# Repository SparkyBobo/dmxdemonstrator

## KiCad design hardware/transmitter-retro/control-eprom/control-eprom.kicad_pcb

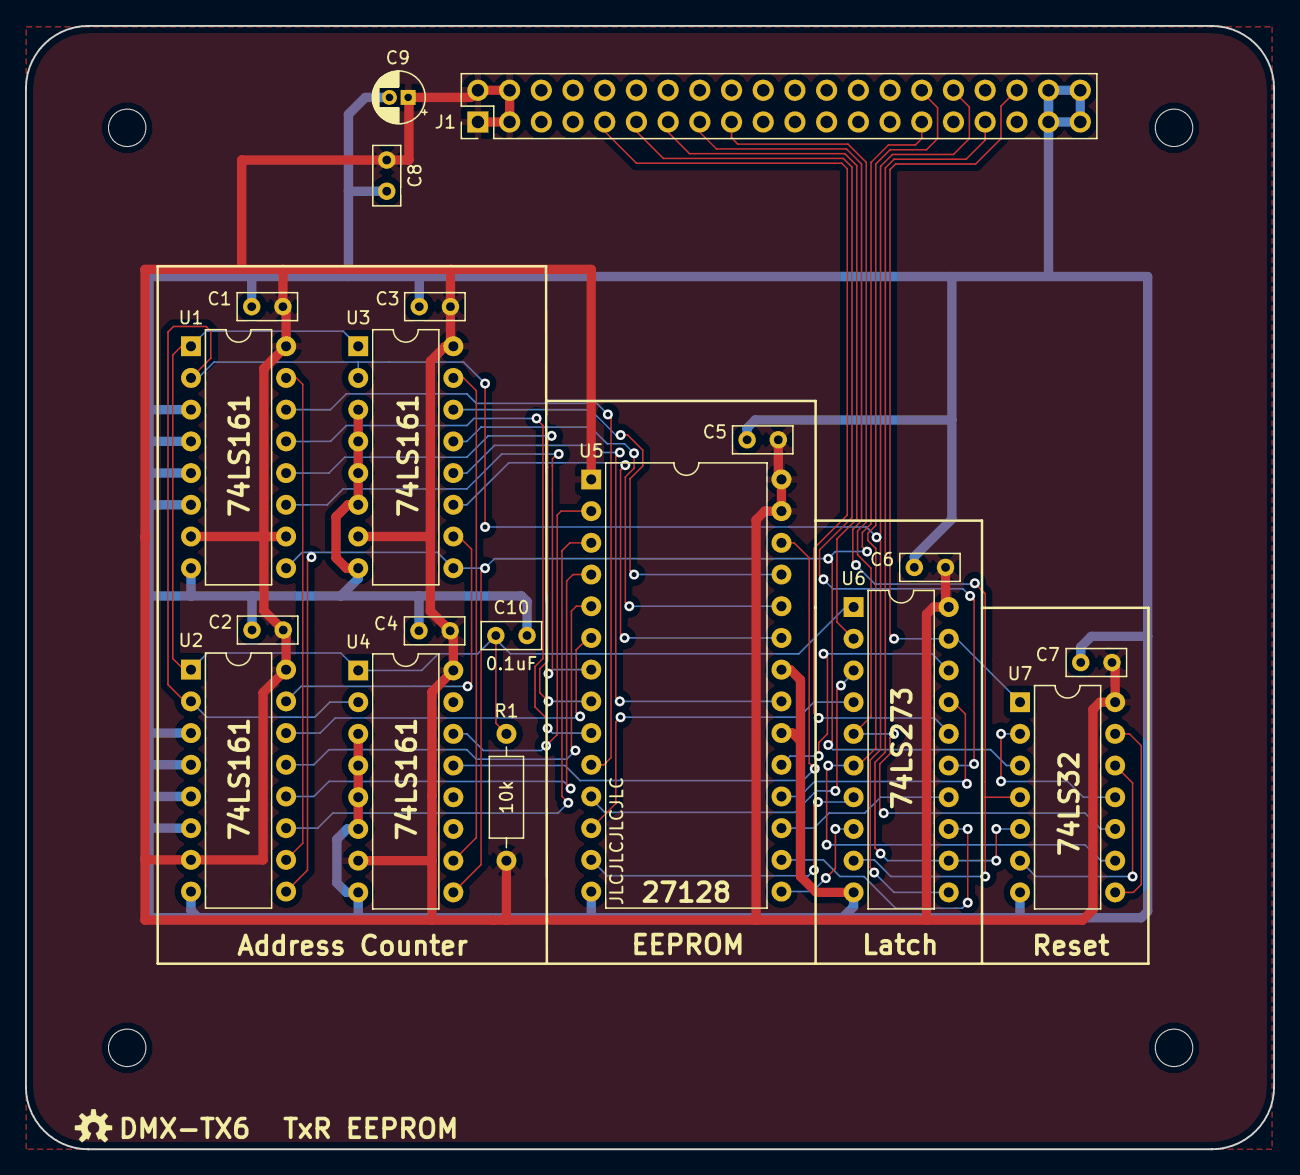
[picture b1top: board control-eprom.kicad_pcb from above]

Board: 2 copper layers, 100.0 x 90.0 mm, 23 parts (0 on the bottom side), 41 nets.

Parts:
C1, C2, C3, C4, C5, C6, C7, C8, C10: 0.1uF; C_Rect_L4.6mm_W2.0mm_P2.50mm_MKS02_FKP02
C9: 10uF; CP_Radial_D4.0mm_P1.50mm
J1: Expansion; PinHeader_2x20_P2.54mm_Vertical
MH1, MH2, MH3, MH4: MountingHole; MountingHole_3mm
R1: 10k; R_Axial_DIN0207_L6.3mm_D2.5mm_P10.16mm_Horizontal
U1, U2, U3, U4: 74LS161; DIP-16_W7.62mm
U5: 27128; DIP-28_W15.24mm
U6: 74LS273; DIP-20_W7.62mm
U7: 74LS32; DIP-14_W7.62mm

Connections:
+5V: C1.1, C2.1, C3.1, C4.1, C5.1, C6.1, C7.1, C8.1, C9.1, J1.1, J1.2, J1.3, J1.4, R1.1, U1.7, U1.10, U1.16, U2.7, U2.16, U3.7, U3.16, U4.7, U4.16, U5.1, U5.27, U5.28, U6.20, U7.14
/CARRY_0: U1.15, U2.10
/CARRY_1: U2.15, U3.10
/CARRY_2: U3.15, U4.10
/CLK_TX: J1.32, U1.2, U2.2, U3.2, U4.2, U6.11
/DATA_FIXED: J1.13, U6.2
/IA0: U1.14, U5.10
/IA1: U1.13, U5.9
/IA2: U1.12, U5.8
/IA3: U1.11, U5.7
/IA4: U2.14, U5.6
/IA5: U2.13, U5.5
/IA6: U2.12, U5.4
/IA7: U2.11, U5.3
/IA8: U3.14, U5.25
/IA9: U3.13, U5.24
/IA10: U3.12, U5.21
/IA11: U3.11, U5.23
/IA12: U4.14, U5.2
/IA13: U4.13, U5.26
/SAMPLE_LATCH: J1.36, U6.19, U7.1
/SAMPLE_SEL0: J1.11, U6.15
/SAMPLE_SEL1: J1.9, U6.16
/SHIFT_TRANSMIT: J1.17, U6.5, U7.10
/~FRAME_RESET: J1.29, U1.9, U2.9, U3.9, U4.9, U7.3
/~SAMPLE_RESET: J1.33, U6.12, U7.5
/~SHIFT_ENABLE: J1.30, U6.6, U7.9
/~SHIFT_LOAD: J1.15, U6.9, U7.4
GND: C1.2, C2.2, C3.2, C4.2, C5.2, C6.2, C7.2, C8.2, C9.2, C10.2, J1.37, J1.38, J1.39, J1.40, U1.3, U1.4, U1.5, U1.6, U1.8, U2.3, U2.4, U2.5, U2.6, U2.8, U3.3, U3.4, U3.5, U3.6, U3.8, U4.3, U4.4, U4.5, U4.6, U4.8, U5.14, U5.20, U5.22, U6.10, U7.7
unnamed: C10.1, R1.2, U1.1, U2.1, U3.1, U4.1, U6.1
unnamed: U5.11, U6.3
unnamed: U5.12, U6.4
unnamed: U5.13, U6.7
unnamed: U5.15, U6.8
unnamed: U5.16, U6.13
unnamed: U5.17, U6.14
unnamed: U5.18, U6.17
unnamed: U5.19, U6.18
unnamed: U7.2, U7.11
unnamed: U7.6, U7.12
unnamed: U7.8, U7.13

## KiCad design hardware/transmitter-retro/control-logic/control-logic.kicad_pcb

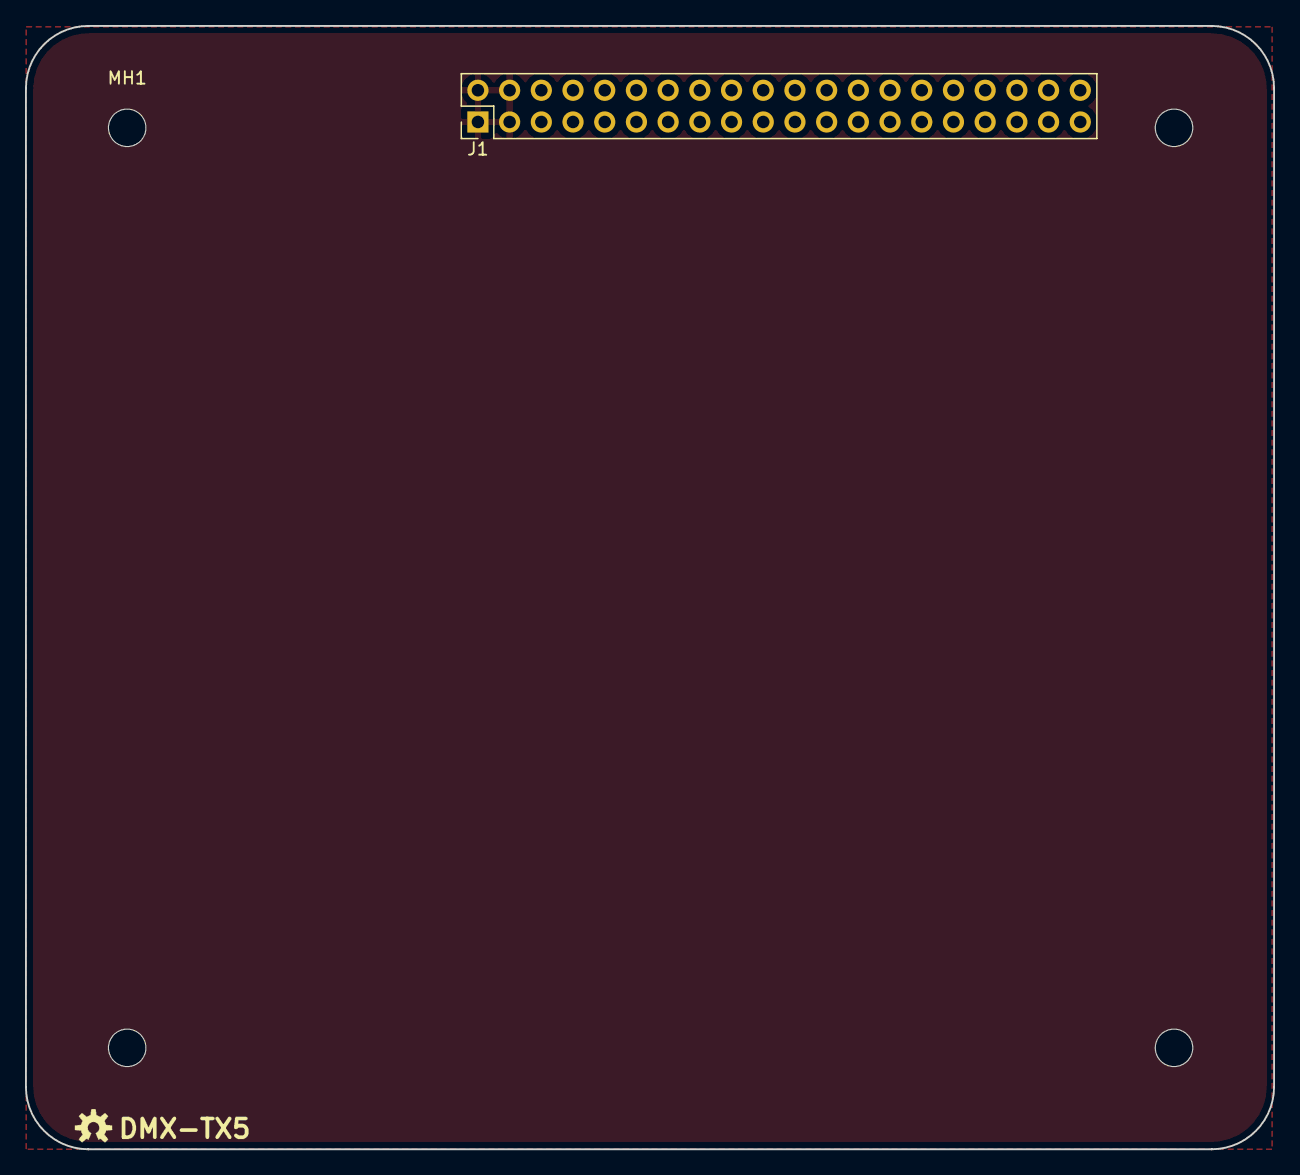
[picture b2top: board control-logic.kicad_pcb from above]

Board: 2 copper layers, 100.0 x 90.0 mm, 5 parts (0 on the bottom side), 2 nets, no tracks yet.

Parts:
J1: Expansion; PinHeader_2x20_P2.54mm_Vertical
MH1, MH2, MH3, MH4: MountingHole; MountingHole_3mm

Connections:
+5V: J1.1, J1.2, J1.3, J1.4
GND: J1.37, J1.38, J1.39, J1.40

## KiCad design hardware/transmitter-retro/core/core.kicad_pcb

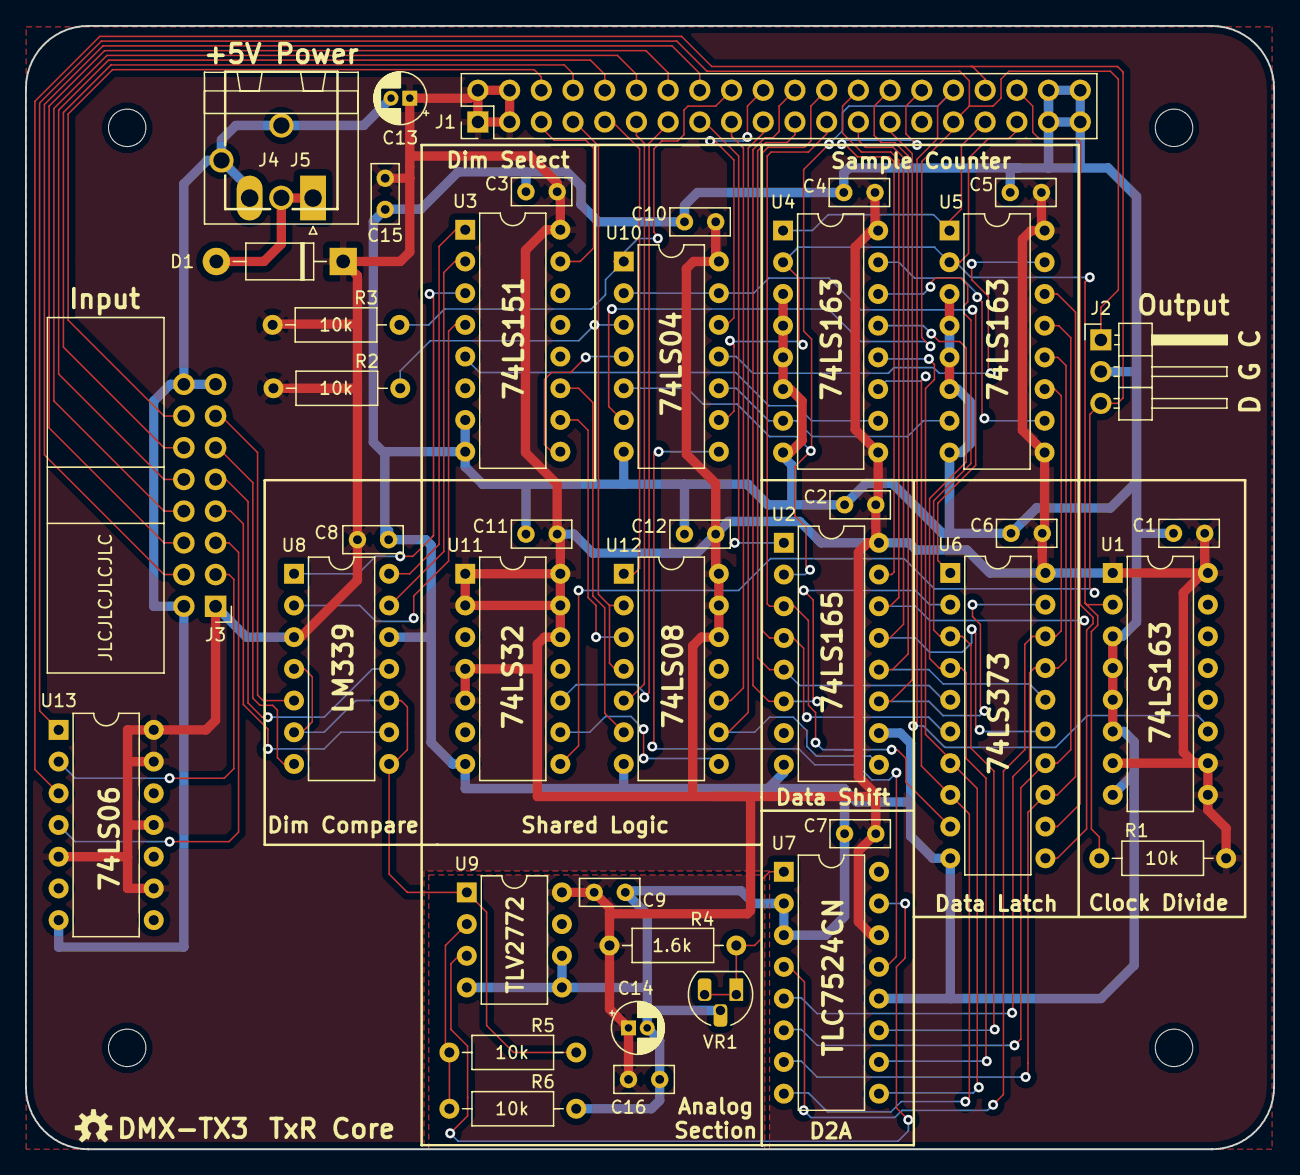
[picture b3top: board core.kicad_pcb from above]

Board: 2 copper layers, 100.0 x 90.0 mm, 46 parts (0 on the bottom side), 66 nets.

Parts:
C1, C2, C3, C4, C5, C6, C7, C8, C9, C10, C11, C12, C15, C16: 0.1uF; C_Rect_L4.6mm_W2.0mm_P2.50mm_MKS02_FKP02
C13, C14: 10uF; CP_Radial_D4.0mm_P1.50mm
D1: 1N5822; D_DO-41_SOD81_P10.16mm_Horizontal
J1: Expansion; PinHeader_2x20_P2.54mm_Vertical
J2: Output; PinHeader_1x03_P2.54mm_Horizontal
J3: Input; IDC-Header_2x08_P2.54mm_Horizontal
J4: Power; PhoenixContact_MSTBA_2,5_2-G-5,08_1x02_P5.08mm_Horizontal
J5: Power; POWER_JACK_PTH_BREAD
MH1, MH2, MH3, MH4: MountingHole; MountingHole_3mm
R1, R2, R3, R5, R6: 10k; R_Axial_DIN0207_L6.3mm_D2.5mm_P10.16mm_Horizontal
R4: 1.6k; R_Axial_DIN0207_L6.3mm_D2.5mm_P10.16mm_Horizontal
U1, U4, U5: 74LS163; DIP-16_W7.62mm
U2: 74LS165; DIP-16_W7.62mm
U3: 74LS151; DIP-16_W7.62mm
U6: 74LS373; DIP-20_W7.62mm
U7: TLC7524CN; DIP-16_W7.62mm
U8: LM339; DIP-14_W7.62mm
U9: TLV2772CP; DIP-8_W7.62mm
U10: 74LS04; DIP-14_W7.62mm
U11: 74LS32; DIP-14_W7.62mm
U12: 74LS08; DIP-14_W7.62mm
U13: 74LS06; DIP-14_W7.62mm
VR1: TL1431; TO-92L_HandSolder

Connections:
+5V: C1.1, C2.1, C3.1, C4.1, C5.1, C6.1, C7.1, C8.1, C9.1, C10.1, C11.1, C12.1, C13.1, C14.1, C15.1, C16.1, D1.1, J1.1, J1.2, J1.3, J1.4, J3.1, R1.2, R2.1, R3.1, R4.2, U1.1, U1.7, U1.9, U1.10, U1.16, U2.16, U3.16, U4.9, U4.16, U5.9, U5.16, U6.20, U7.14, U8.3, U9.8, U10.14, U11.1, U11.2, U11.4, U11.5, U11.12, U11.13, U11.14, U12.12, U12.13, U12.14, U13.5, U13.9, U13.11, U13.13, U13.14
/CLK_RX: J1.31, J2.1, U10.6, U13.1
/CLK_SAMPLE: J1.35, R1.1, U1.2, U4.2, U5.2, U10.9
/CLK_TX: J1.32, U1.11, U2.2, U10.5
/D0: J1.22, U2.6, U6.2
/D1: J1.21, U2.5, U6.5
/D2: J1.24, U2.4, U6.6
/D3: J1.23, U2.3, U6.9
/D4: J1.26, U2.14, U6.12
/D5: J1.25, U2.13, U6.15
/D6: J1.28, U2.12, U6.16
/D7: J1.27, U2.11, U6.19
/DATA_FIXED: J1.13, U11.10
/DATA_RX: J1.34, J2.3, U11.8, U13.3
/DATA_SHIFT: J1.19, U2.9, U12.9
/DIM1: J3.7, U8.9
/DIM2: J3.9, U8.11
/DIM3: J3.11, U8.7
/DIM4: J3.13, U8.5
/SAMPLE_COUNT: J1.5, U3.15
/SAMPLE_LATCH: J1.36, U6.11
/SAMPLE_SEL0: J1.11, U12.5
/SAMPLE_SEL1: J1.9, U12.1
/SHIFT_TRANSMIT: J1.17, U12.10
/SPD_HI: J1.16, J3.4
/SPD_LO: J1.12, J3.8
/SPD_MID: J1.14, J3.6
/sample/DO0: U4.14, U6.3, U7.11
/sample/DO1: U4.13, U6.4, U7.10
/sample/DO2: U4.12, U6.7, U7.9
/sample/DO3: U4.11, U6.8, U7.8
/sample/DO4: U5.14, U6.13, U7.7
/sample/DO5: U5.13, U6.14, U7.6
/sample/DO6: U5.12, U6.17, U7.5
/sample/DO7: U5.11, U6.18, U7.4
/~BUS_ACK: J1.20, U10.12
/~BUS_REQ: J1.18, R3.2, U10.1
/~CLK_FST: J1.6, J3.14
/~CLK_SLO: J1.8, J3.12
/~CLK_STEP: J1.10, J3.10
/~CLOCK: J3.3, U13.2
/~DATA: J3.5, U13.4
/~SAMPLE_OVERRIDE: J1.7, R2.2, U10.3, U12.2, U12.4
/~SAMPLE_RESET: J1.33, U4.1, U5.1
/~SHIFT_ENABLE: J1.30, U2.15
/~SHIFT_LOAD: J1.15, U2.1
GND: C1.2, C2.2, C3.2, C4.2, C5.2, C6.2, C7.2, C8.2, C9.2, C10.2, C11.2, C12.2, C13.2, C14.2, C15.2, C16.2, J1.37, J1.38, J1.39, J1.40, J2.2, J3.2, J3.15, J3.16, J4.2, J5.GND, J5.GNDB, R6.1, U1.3, U1.4, U1.5, U1.6, U1.8, U2.8, U2.10, U3.7, U3.8, U4.3, U4.4, U4.5, U4.6, U4.8, U5.3, U5.4, U5.5, U5.6, U5.8, U6.10, U7.2, U7.3, U7.12, U8.12, U9.4, U9.5, U9.6, U10.7, U11.7, U12.7, U13.7, VR1.2
unnamed: D1.2, J4.1, J5.PWR
unnamed: R4.1, U7.1, VR1.1, VR1.3
unnamed: R5.1, R6.2, U9.2
unnamed: R5.2, U8.4, U8.6, U8.8, U8.10, U9.1
unnamed: U3.1, U8.14
unnamed: U3.2, U8.13
unnamed: U3.3, U8.1
unnamed: U3.4, U8.2
unnamed: U3.5, U4.10
unnamed: U4.15, U5.10
unnamed: U7.15, U9.3
unnamed: U3.9, U10.4
unnamed: U7.13, U10.8
unnamed: U4.7, U5.7, U10.10
unnamed: U5.15, U10.11
unnamed: U6.1, U10.2, U10.13
unnamed: U11.9, U12.8
unnamed: U3.10, U12.3
unnamed: U3.11, U12.6

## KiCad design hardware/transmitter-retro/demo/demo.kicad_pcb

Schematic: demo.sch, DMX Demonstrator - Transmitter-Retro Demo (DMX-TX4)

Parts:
A1: Monitor; Arduino_Nano
J1: Expansion; PinHeader_2x20_P2.54mm_Vertical
NT1: Tie; NetTie-2_THT_Pad0.3mm

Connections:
+5V: A1.3 (RESET), A1.28 (RESET), J1.1, J1.2, J1.3, J1.4, NT1.2; also elsewhere on the board
/CLK_RX: A1.16 (D13), J1.31; also elsewhere on the board
/CLK_SAMPLE: J1.35; also elsewhere on the board
/D0: A1.26 (A7), J1.22
/D1: A1.25 (A6), J1.21
/D2: A1.24 (A5), J1.24
/D3: A1.23 (A4), J1.23
/D4: A1.22 (A3), J1.26
/D5: A1.21 (A2), J1.25
/D6: A1.20 (A1), J1.28
/D7: A1.19 (A0), J1.27
/DATA_RX: A1.15 (D12), J1.34
/SAMPLE_LATCH: A1.12 (D9), J1.36
/SAMPLE_SEL0: A1.6 (D3), J1.11
/SAMPLE_SEL1: A1.5 (D2), J1.9
/SHIFT_TRANSMIT: A1.9 (D6), J1.17
/SPD_LO: J1.12; also elsewhere on the board
/SPD_MID: J1.14; also elsewhere on the board
/step/~CLK_S0_IN: A1.13 (D10); also elsewhere on the board
/step/~CLK_S1_IN: A1.14 (D11); also elsewhere on the board
/step/~CLK_STEPB_IN: A1.1 (D1/TX); also elsewhere on the board
/~CLK_FST: J1.6; also elsewhere on the board
/~CLK_SLO: J1.8; also elsewhere on the board
/~CLK_STEP: J1.10; also elsewhere on the board
/~FRAME_RESET: A1.7 (D4), J1.29
/~SAMPLE_RESET: A1.11 (D8), J1.33
/~SHIFT_ENABLE: A1.10 (D7), J1.30
/~SHIFT_LOAD: A1.8 (D5), J1.15
GND: A1.4 (GND), A1.29 (GND), J1.37, J1.38, J1.39, J1.40; also elsewhere on the board
unnamed: A1.27 (+5V), NT1.1

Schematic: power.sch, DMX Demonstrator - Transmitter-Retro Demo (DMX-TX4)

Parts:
C1, C2, C3, C4, C5, C6, C7, C11, C12: 0.1uF; C_Rect_L4.6mm_W2.0mm_P2.50mm_MKS02_FKP02
C9, C10: 10uF; CP_Radial_D4.0mm_P1.50mm
MH1, MH2, MH3, MH4: MountingHole; MountingHole_3mm
U3, U4, U5: 74LS74; DIP-14_W7.62mm
U6: 74LS08; DIP-14_W7.62mm
U7: 74LS32; DIP-14_W7.62mm

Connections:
+5V: C1.1, C2.1, C3.1, C4.1, C5.1, C6.1, C7.1, C9.1, C10.1, C11.1, C12.1, U3.4, U3.10, U3.14, U4.4, U4.10, U4.14, U5.4, U5.14, U6.12, U6.13, U6.14, U7.1, U7.2, U7.4, U7.5, U7.12, U7.13, U7.14; also elsewhere on the board
/CLK_RX: U5.11; also elsewhere on the board
/step/CLK_FAST_IN: U3.3, U3.11, U4.3, U4.11, U5.3; also elsewhere on the board
/step/CLK_SEND_ENABLE: U5.1, U5.8
/step/CLK_STEP_MODE: U6.3, U6.9
/step/CLK_STEP_OUT: U5.5; also elsewhere on the board
/step/~CLK_S0_IN: U3.5, U6.1; also elsewhere on the board
/step/~CLK_S1_IN: U3.9, U6.2; also elsewhere on the board
/step/~CLK_STEPB_IN: U6.4; also elsewhere on the board
/step/~CLK_STEPIN: U4.5, U4.12, U7.9
/step/~CLK_STEP_PULSE: U5.13, U6.8
/~CLK_FST: U3.12; also elsewhere on the board
/~CLK_SLO: U3.2; also elsewhere on the board
/~CLK_STEP: U6.5; also elsewhere on the board
GND: C1.2, C2.2, C3.2, C4.2, C5.2, C6.2, C7.2, C9.2, C10.2, C11.2, C12.2, U3.7, U4.7, U5.7, U6.7, U7.7; also elsewhere on the board
unnamed 44: U3.1, U3.13; also elsewhere on the board
unnamed 45: U4.1, U4.13, U5.10, U5.12; also elsewhere on the board
unnamed: U4.2, U6.6
unnamed: U4.8, U7.10
unnamed: U5.2, U5.6
unnamed: U6.10, U7.8

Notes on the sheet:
Logic IC Power
Decoupling Capacitors
Unused Gates

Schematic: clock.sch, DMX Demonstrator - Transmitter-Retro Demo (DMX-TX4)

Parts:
C13: 0.47uF; C_Rect_L4.6mm_W2.0mm_P2.50mm_MKS02_FKP02
C14, C15, C17: 0.1uF; C_Rect_L4.6mm_W2.0mm_P2.50mm_MKS02_FKP02
C16: .001uF; C_Rect_L4.6mm_W2.0mm_P2.50mm_MKS02_FKP02
R2: 100; R_Axial_DIN0207_L6.3mm_D2.5mm_P10.16mm_Horizontal
R3: 330; R_Axial_DIN0207_L6.3mm_D2.5mm_P10.16mm_Horizontal
R4, R5, R6, R7, R8: 10k; R_Axial_DIN0207_L6.3mm_D2.5mm_P10.16mm_Horizontal
U1: 556; DIP14
U2: 74LS151; DIP-16_W7.62mm
U3: 74LS74; DIP-14_W7.62mm

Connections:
+5V: R3.1, R4.1, R6.1, R7.1, R8.1, U1.4, U1.10, U1.14, U2.4, U2.12, U2.13, U2.14, U2.15, U2.16, U3.4, U3.10, U3.14; also elsewhere on the board
/CLK_SAMPLE: U2.5; also elsewhere on the board
/SPD_LO: C13.1, U1.2, U1.6; also elsewhere on the board
/SPD_MID: R2.2; also elsewhere on the board
/clock/CLK_SLOW: U1.5, U2.2
/step/CLK_FAST_IN: U1.9, U2.3, U3.3, U3.11; also elsewhere on the board
/step/CLK_STEP_OUT: U2.1; also elsewhere on the board
/step/~CLK_S0_IN: U2.11, U3.5; also elsewhere on the board
/step/~CLK_S1_IN: U2.10, U3.9; also elsewhere on the board
/~CLK_FST: R7.2, U3.12; also elsewhere on the board
/~CLK_SLO: R6.2, U3.2; also elsewhere on the board
GND: C13.2, C14.2, C15.2, C16.2, C17.2, U1.7, U2.7, U2.8, U2.9, U3.7; also elsewhere on the board
unnamed: C14.1, U1.3
unnamed: C15.1, U1.11
unnamed: C16.1, R5.2, U1.8, U1.12
unnamed: C17.1, R8.2, U3.1, U3.13
unnamed: R2.1, R3.2, U1.1
unnamed: R4.2, R5.1, U1.13

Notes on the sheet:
Clock Multiplexer: S0=0,S1=0: Off S0=1,S1=0: Fast S0=0,S1=1: Slow/Adj S0=1,S1=1: Step
Fast Clock 48kHz
Slow/Adj Clock 13Hz-3.3kHz
To external 100k potentiometer
S0 and S1 are set on the rising edge of CLK_FAST for a clean transition between speeds on the falling edge of CLK_SAMPLE.

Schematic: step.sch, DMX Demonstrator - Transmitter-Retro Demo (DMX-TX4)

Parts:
C18: 0.1uF; C_Rect_L4.6mm_W2.0mm_P2.50mm_MKS02_FKP02
R9, R10, R11: 10k; R_Axial_DIN0207_L6.3mm_D2.5mm_P10.16mm_Horizontal
U4, U5: 74LS74; DIP-14_W7.62mm
U6: 74LS08; DIP-14_W7.62mm
U7: 74LS32; DIP-14_W7.62mm

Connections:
+5V: R9.1, R10.1, R11.1, U4.4, U4.10, U4.14, U5.4, U5.14, U6.12, U6.13, U6.14, U7.1, U7.2, U7.4, U7.5, U7.12, U7.13, U7.14; also elsewhere on the board
/CLK_RX: U5.11; also elsewhere on the board
/step/CLK_FAST_IN: U4.3, U4.11, U5.3; also elsewhere on the board
/step/CLK_SEND_ENABLE: U5.1, U5.8
/step/CLK_STEP_MODE: U6.3, U6.9
/step/CLK_STEP_OUT: U5.5; also elsewhere on the board
/step/~CLK_S0_IN: U6.1; also elsewhere on the board
/step/~CLK_S1_IN: U6.2; also elsewhere on the board
/step/~CLK_STEPB_IN: R10.2, U6.4; also elsewhere on the board
/step/~CLK_STEPIN: U4.5, U4.12, U7.9
/step/~CLK_STEP_PULSE: U5.13, U6.8
/~CLK_STEP: R9.2, U6.5; also elsewhere on the board
GND: C18.2, U4.7, U5.7, U6.7, U7.7; also elsewhere on the board
unnamed: C18.1, R11.2, U4.1, U4.13, U5.10, U5.12
unnamed: U4.2, U6.6
unnamed: U4.8, U7.10
unnamed: U5.2, U5.6
unnamed: U6.10, U7.8

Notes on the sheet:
CLK_FAST_IN ~CLK_STEPA/B_IN~ ~CLK_STEPIN~ U4B ~Q~ ~CLK_STEP_PULSE~ CLK_STEP_MODE CLK_SEND_ENABLE CLK_STEP_OUT CLK_RX_IN

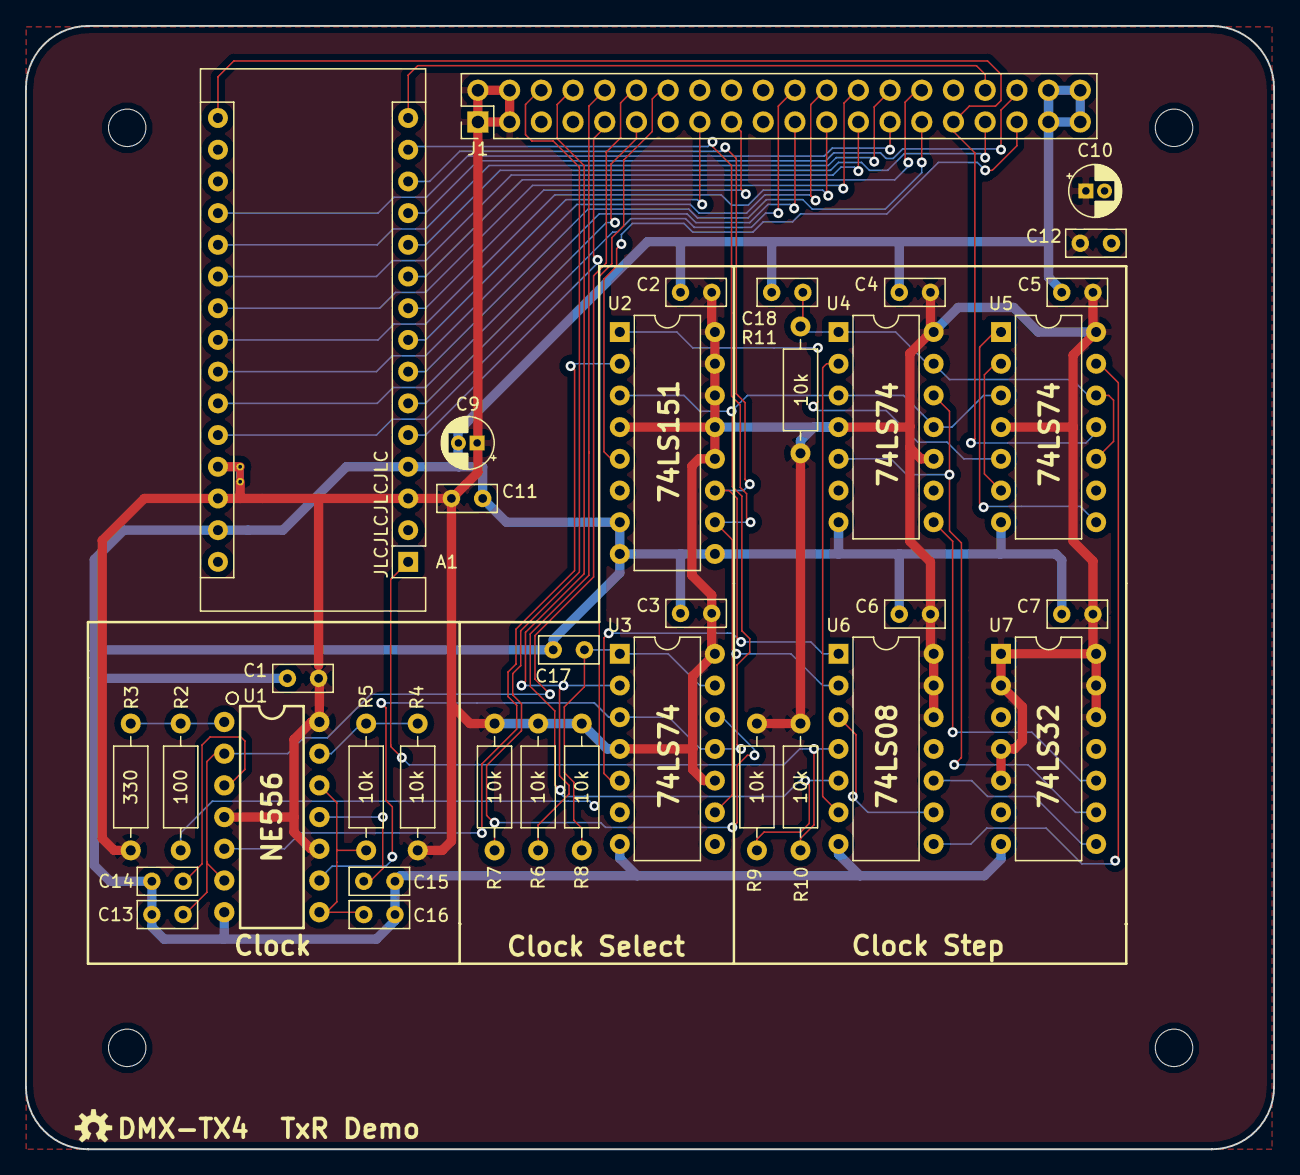
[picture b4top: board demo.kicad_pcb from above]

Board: 2 copper layers, 100.0 x 90.0 mm, 41 parts (0 on the bottom side), 48 nets.

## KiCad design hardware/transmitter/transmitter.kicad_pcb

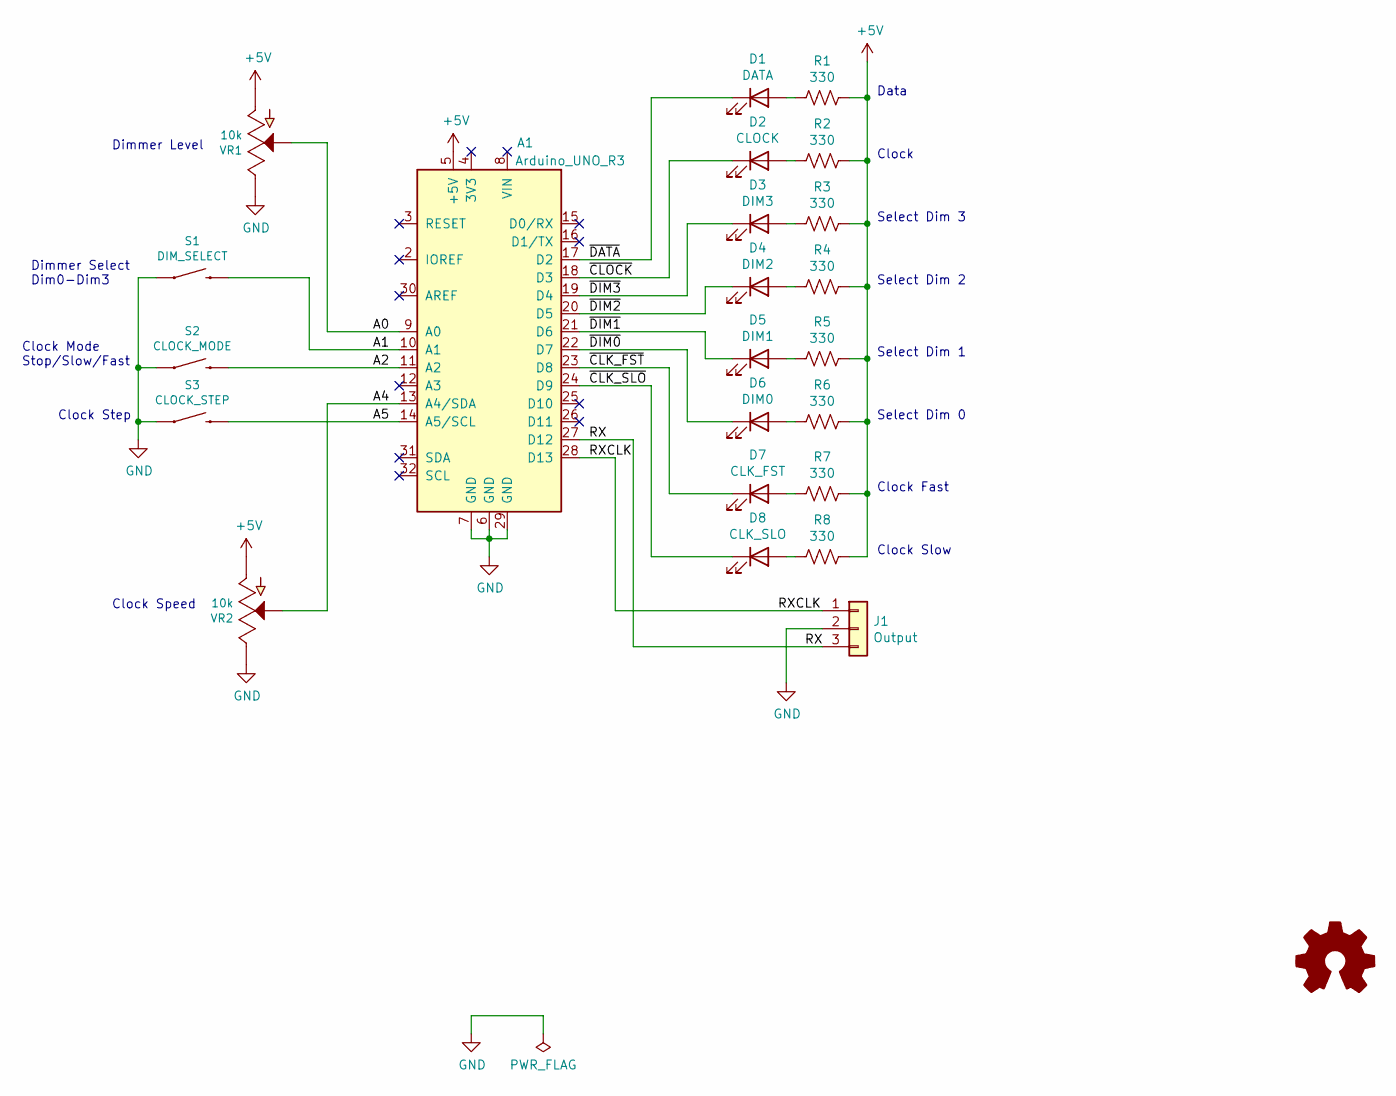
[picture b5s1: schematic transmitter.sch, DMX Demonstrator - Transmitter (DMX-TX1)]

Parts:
A1: Arduino_UNO_R3; ARDUINO_R3_NO_HOLES
D1: DATA; LED_D5.0mm
D2: CLOCK; LED_D5.0mm
D3: DIM3; LED_D5.0mm
D4: DIM2; LED_D5.0mm
D5: DIM1; LED_D5.0mm
D6: DIM0; LED_D5.0mm
D7: CLK_FST; LED_D5.0mm
D8: CLK_SLO; LED_D5.0mm
J1: Output; PinHeader_1x03_P2.54mm_Horizontal
R1, R2, R3, R4, R5, R6, R7, R8: 330; R_Axial_DIN0207_L6.3mm_D2.5mm_P10.16mm_Horizontal
S1: DIM_SELECT; TACTILE_SWITCH_PTH_12MM
S2: CLOCK_MODE; TACTILE_SWITCH_PTH_12MM
S3: CLOCK_STEP; TACTILE_SWITCH_PTH_12MM
VR1: 10k; SLIDER-SMALL
VR2: 10k; POT-PTH-ALPS

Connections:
+5V: A1.5 (+5V), R1.1, R2.1, R3.1, R4.1, R5.1, R6.1, R7.1, R8.1, VR1.BOTT (A), VR2.P$3 (A)
/A0: A1.9 (A0), VR1.WIPE (S)
/A1: A1.10 (A1), S1.3 (2)
/A2: A1.11 (A2), S2.3 (2)
/A4: A1.13 (A4/SDA), VR2.P$2 (S)
/A5: A1.14 (A5/SCL), S3.3 (2)
/RX: A1.27 (D12), J1.3
/RXCLK: A1.28 (D13), J1.1
/~CLK_FST: A1.23 (D8), D7.1 (K)
/~CLK_SLO: A1.24 (D9), D8.1 (K)
/~CLOCK: A1.18 (D3), D2.1 (K)
/~DATA: A1.17 (D2), D1.1 (K)
/~DIM0: A1.22 (D7), D6.1 (K)
/~DIM1: A1.21 (D6), D5.1 (K)
/~DIM2: A1.20 (D5), D4.1 (K)
/~DIM3: A1.19 (D4), D3.1 (K)
GND: A1.6 (GND), A1.7 (GND), A1.29 (GND), J1.2, S1.1, S2.1, S3.1, VR1.TOP (E), VR2.P$1 (E)
unnamed: D1.2 (A), R1.2
unnamed: D2.2 (A), R2.2
unnamed: D3.2 (A), R3.2
unnamed: D4.2 (A), R4.2
unnamed: D5.2 (A), R5.2
unnamed: D6.2 (A), R6.2
unnamed: D7.2 (A), R7.2
unnamed: D8.2 (A), R8.2

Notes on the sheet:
Dimmer Select Dim0-Dim3
Dimmer Level
Clock Speed
Clock Mode Stop/Slow/Fast
Select Dim 1
Select Dim 0
Select Dim 3
Select Dim 2
Clock Step
Clock Slow
Clock Fast
Clock
Data

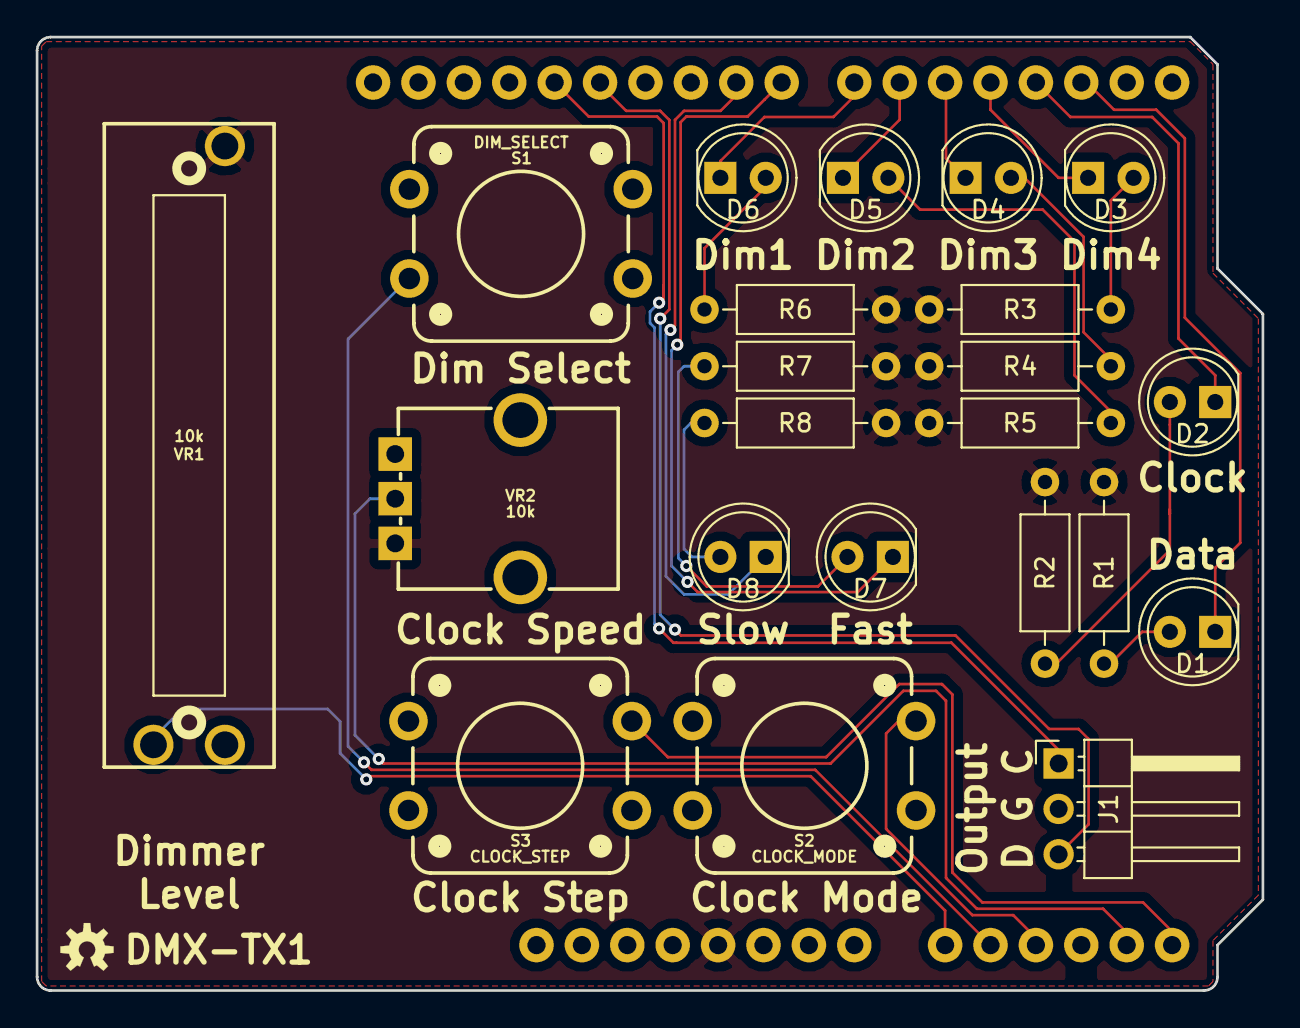
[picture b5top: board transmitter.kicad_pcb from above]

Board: 2 copper layers, 68.6 x 53.3 mm, 23 parts (0 on the bottom side), 25 nets.

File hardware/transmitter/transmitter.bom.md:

# Bill Of Materials (BOM)

## Schematic

**Filename:** E:\OpenSource\dmxdemonstrator\hardware\transmitter\transmitter.sch

**Date Modified:** 3/31/2024 7:18:02 PM

**Kicad Version:** Eeschema (5.1.12)-1

**Component Count:** 23

## Components

Item#|Quantity|Reference|Description|Manufacturer|Part Number|Datasheet|Notes
-----|--------|---------|-----------|------------|-----------|---------|-----
1|1|PCB|Transmitter PCB|OHSPark|DMX-TX1, Rev Rev 1.3||[Order](https://oshpark.com/shared_projects/BYd66lVx)|
2|1|A1|Arduino UNO/Leonardo||||
3|1|A1|Arduino R3 Headers||||
4|1|D1|Green LED, 5mm||||
5|1|D2|Red LED, 5mm||||
6|1|D3|Multicolor LED Kit, 5mm||||
7|1|D4|Multicolor LED Kit, 5mm||||
8|1|D5|Multicolor LED Kit, 5mm||||
9|1|D6|Multicolor LED Kit, 5mm||||
10|1|D7|Red LED, 5mm||||
11|1|D8|Green LED, 5mm||||
12|1|J1|3-pin right-angle header||||
13|8|R1, R2, R3, R4, R5, R6, R7, R8|330 ohm||||
14|1|S1|Momentary switch, 12mm||||
15|1|S2|Momentary switch, 12mm||||
16|1|S3|Momentary switch, 12mm||||
17|1|VR1|10k slide potentiometer||||
18|1|VR1|slide potentiometer knob||||
19|1|VR2|10k potentiometer, linear|Bourns|PTV09A-4020F-B103||
<!--BOMROW-->

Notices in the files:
hardware/transmitter-retro/control-eprom/control-eprom.kicad_pcb:
https://creativecommons.org/licenses/by-sa/4.0
Released under the Creative Commons Attribution Share-Alike 4.0 License
